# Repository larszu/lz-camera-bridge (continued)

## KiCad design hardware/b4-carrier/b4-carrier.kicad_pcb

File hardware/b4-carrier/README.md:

# B4 lens carrier board v1

A 184 × 100 mm two-layer carrier for the bench circuit in
[`docs/b4/iris-anleitung.html`](../../docs/b4/iris-anleitung.html): everything
that was loose on two breadboards on 2026-10-10, on one board with plug-in
modules and locking connectors.

**Status: generated, not built.** Fully routed (Freerouting, 0 open
connections); KiCad DRC has no errors apart from the deliberate triple ESP32 row
(see below), only silkscreen warnings. Nothing on this board has been powered.
Measure the first one before a lens is connected.

There is **no KiCad schematic** (`.kicad_sch`) yet: the netlist lives in
`generate_pcb.py`, one `place()` / `res()` call per part with its nets — that is
the reviewable source. The stage formulas are in the table below.

## What is on it

| Block | Parts | Why |
|---|---|---|
| Power in | USB-C with **CH224A** (24 kΩ on CFG1 = 12 V, WCH datasheet table 5-1), or a 5.5/2.1 mm DC jack; both through 1N5822 Schottky diodes | PD supply like the bench, DC as a fallback |
| Protection | Polyfuse MF-RHT200 (2 A hold), TVS P6KE18A, 470 µF bulk | Motor current spikes, short, over-voltage |
| 9 V | L7809 + 330 nF / 100 nF / 10 µF | Replaces the 330 Ω / 1 kΩ divider; the zoom stop hung on that voltage |
| 5 V | RECOM R-78E5.0-0.5 switcher → ESP32 VIN through 1N5819 | The ESP32's USB can stay plugged in |
| 3.3 V (quiet) | LP2950CZ-3.3 from 5 V | DAC, ADC, OLED, pots and the iris offset, separate from the ESP32's noisy 3.3 V |
| Op-amps | **LM324** in a socket | A: iris stage as on the bench. B: zoom. C: focus. D: unused, tied off |
| Zoom / focus drive | Difference amplifier `Vout = REF + 1.8 · (V_B − V_C)` with 100k/180k, REF = the demand socket's own 5 V centre (zoom socket pin 7); simulated in [`simulation/`](simulation/README.md) | "Stop" is now the lens's own reference when DAC B = DAC C, instead of a code that wandered 1270 … 1790 on the bench |
| Readback | 100 k / 68 k + 100 nF into ADS1115 A0–A3 (iris position, zoom position, focus position, iris setpoint) | As measured on the bench |
| Modules | **Either** ESP32 DevKit V1 (30 pin) **or** Waveshare ESP32-S3-ETH (with or without PoE module), Adafruit MCP4728, ADS1115 breakout, 0.96″ SSD1306 OLED — all on sockets | Swappable, and the DevKit's USB stays reachable |
| Pots | Three on-board 10 k (Alps RK09K: iris, zoom, focus), three JST-XH for external pots; jumpers JP2 / JP3 / JP4 choose on-board or external | Bench test without anything plugged in |
| Connectors | JST-XH, locking | Loose Dupont wires caused every fault on the bench |

## Connectors

| Ref | To | Pins (1 → n) |
|---|---|---|
| J3 | Lens Hirose 12-pin | +12 V (pin 6) · GND (3) · iris control (5) · iris position (7) · remote (8) · zoom position (10) · focus position (11) · pin 12 |
| J7 | Black zoom socket on the grip | GND · pin 6 (speed) · pin 7 (5 V centre, **REF**) · pin 9 (position) |
| J8 | Focus module socket | GND · control · REF · position — **pinout still to be measured** |
| J4 / J5 / J6 | External pots iris / zoom / focus | 3.3 V · wiper · GND |
| JP1 | Jumper: iris remote | On = pin 8 at 5 V through 1 kΩ |

## ESP32 DevKit V1: three widths

DOIT DevKit V1 clones exist with 22.86, 25.40 and 27.94 mm between the pin
rows. The 3V3 row (J10) is fixed; the VIN row is laid out three times (J11–J13).
**Solder a socket into only the one that fits your board.** DRC reports the
three as overlapping courtyards — that is intended. Measure: centre of one pin
row to the centre of the other.

## Waveshare ESP32-S3-ETH instead of the DevKit

J14 / J15: 2 × 20 pins, rows 17.78 mm apart, front side (RJ45) up, RJ45 end
towards the top edge (Waveshare's dimension drawing). The optional PoE module
plugs onto the 6-pin header on the top side, so it does not touch the carrier.
Connections: VSYS ← 5 V (through D4), IO16 SDA, IO17 SCL, IO1 / IO2 / IO3 the
iris / zoom / focus pots (camera-header pins — free while no camera is fitted).
The lens still needs the board's 12 V; PoE only powers the ESP32 board.
**Fit only one ESP32 board.**

## Firmware changes this board needs

* Zoom: DAC C fixed at mid-scale (2048); zoom speed = DAC B − DAC C. The stored
  stop becomes ≈ 2048 and should no longer wander; the position hold stays as
  a safety net.
* Focus: DAC D against DAC C, same scheme.
* OLED: SSD1306 on the existing I²C bus (0x3C) — WLAN, IP, iris ≈ F, zoom ≈ mm.
* Pots: DevKit GPIO 34 / 35 / 36, S3-ETH GPIO 1 / 2 / 3.

## Regenerate

```
/Applications/KiCad/KiCad.app/Contents/Frameworks/Python.framework/Versions/3.9/bin/python3 \
    hardware/b4-carrier/generate_pcb.py --route
```

Needs KiCad 10, Java (`brew install openjdk`) and Freerouting in `.tools/`
(not committed). The script writes the board, `bom.csv` and routes it.
`fab/` holds the files for PCBWay:

| File | What |
|---|---|
| `fab/b4-carrier-gerber.zip` | Gerbers + Excellon drill, upload as is |
| `fab/bom-smt.csv`, `fab/cpl-smt.csv` | SMT assembly of J1, U1, R1, C1 only |
| `bom.csv` | Every part with value and footprint, for ordering the through-hole parts |
| `fab/render-top.png`, `fab/render-bottom.png` | 3D renders |
| `fab/top-assembly.pdf` | Top copper, silkscreen and the module outlines (F.Fab) for placing parts |

Module outlines (ESP32, MCP4728, ADS1115) are drawn on F.Fab so nothing tall
ends up under a module on its header. The ADS1115 body is assumed to lie left of
its header (header on the module's right edge, VDD at the bottom) as on the
module used on the bench — check yours.

## Before ordering

1. Open `b4-carrier.kicad_pcb` in KiCad, look at every connector against the
   part you have (OLED pin order varies between modules!).
2. Check the ESP32 row width on your DevKit.
3. Order 2-layer, 1.6 mm, HASL, with **SMT assembly for J1, U1, R1, C1 only**
   (USB-C, CH224A and its two parts); everything else is through-hole.

## Ideas for v2 (not on this board)

* **Outputs off at power-up:** an analog switch (e.g. 74HC4066) in pin 5 and the
  zoom/focus lines, enabled by the firmware once the DAC holds sane values — no
  twitch while the ESP32 boots.
* **Lens current monitor** (INA219 on the I²C bus): a jammed servo or a short
  shows up as current, not as a burnt polyfuse.
* **VTR / RET buttons** to the lens via PC817 optocouplers (in stock).
* **ESD protection** (TVS array) on every line that leaves the board.
* A **touch panel** as a separate device using the HTTP API (see the B4 docs).

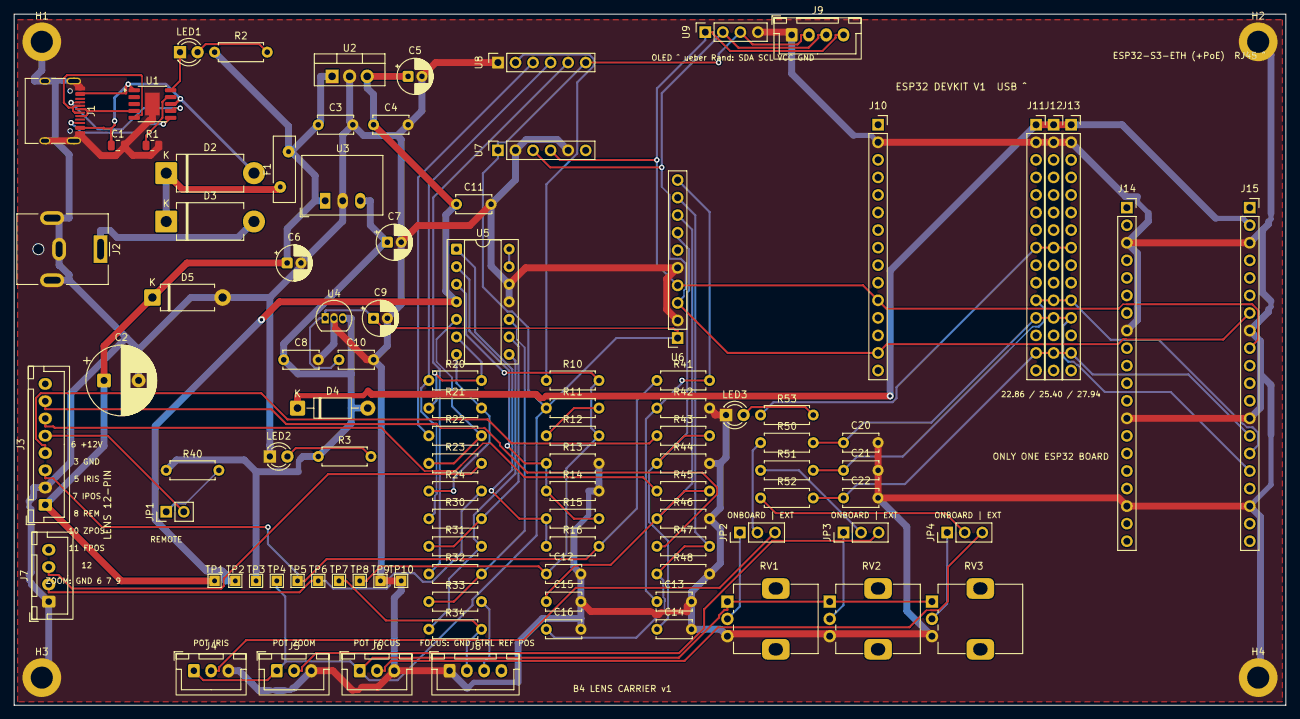
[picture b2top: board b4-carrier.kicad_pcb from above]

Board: 2 copper layers, 184.0 x 100.0 mm, 105 parts (0 on the bottom side), 62 nets.

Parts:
C1: 1uF 25V; C_0805_2012Metric
C2: 470uF 25V; CP_Radial_D10.0mm_P5.00mm
C3: 330nF; C_Disc_D5.0mm_W2.5mm_P5.00mm
C4, C10, C11, C12, C13, C14, C15, C16, C20, C21, C22: 100nF; C_Disc_D5.0mm_W2.5mm_P5.00mm
C5, C6: 10uF 25V; CP_Radial_D5.0mm_P2.00mm
C7: 22uF 16V; CP_Radial_D5.0mm_P2.00mm
C8: 1uF; C_Disc_D5.0mm_W2.5mm_P5.00mm
C9: 10uF 16V; CP_Radial_D5.0mm_P2.00mm
D2, D3: 1N5822; D_DO-201AD_P12.70mm_Horizontal
D4: 1N5819; D_DO-41_SOD81_P10.16mm_Horizontal
D5: P6KE18A; D_DO-15_P10.16mm_Horizontal
F1: MF-RHT200; Fuse_Bourns_MF-RHT200
H1, H2, H3, H4: M3; MountingHole_3.2mm_M3_DIN965_Pad
J1: USB-C PD 12V; USB_C_Receptacle_HRO_TYPE-C-31-M-12
J2: DC 12V; BarrelJack_CUI_PJ-063AH_Horizontal
J3: LENS 12-pin; JST_XH_B8B-XH-A_1x08_P2.50mm_Vertical
J4: POT IRIS; JST_XH_B3B-XH-A_1x03_P2.50mm_Vertical
J5: POT ZOOM; JST_XH_B3B-XH-A_1x03_P2.50mm_Vertical
J6: POT FOCUS; JST_XH_B3B-XH-A_1x03_P2.50mm_Vertical
J7: ZOOM DEMAND; JST_XH_B4B-XH-A_1x04_P2.50mm_Vertical
J8: FOCUS DEMAND; JST_XH_B4B-XH-A_1x04_P2.50mm_Vertical
J9: OLED cable; JST_XH_B4B-XH-A_1x04_P2.50mm_Vertical
J10: ESP32 L; PinSocket_1x15_P2.54mm_Vertical
J11: ESP32 R 22.86; PinSocket_1x15_P2.54mm_Vertical
J12: ESP32 R 25.40; PinSocket_1x15_P2.54mm_Vertical
J13: ESP32 R 27.94; PinSocket_1x15_P2.54mm_Vertical
J14: S3-ETH IO20 row; PinSocket_1x20_P2.54mm_Vertical
J15: S3-ETH VBUS row; PinSocket_1x20_P2.54mm_Vertical
JP1: REMOTE; PinHeader_1x02_P2.54mm_Vertical
JP2: IRIS POT; PinHeader_1x03_P2.54mm_Vertical
JP3: ZOOM POT; PinHeader_1x03_P2.54mm_Vertical
JP4: FOCUS POT; PinHeader_1x03_P2.54mm_Vertical
LED1: green; LED_D3.0mm
LED2: red; LED_D3.0mm
LED3: blue; LED_D3.0mm
R1: 24k 1%; R_0805_2012Metric
R2: 4.7k; R_Axial_DIN0207_L6.3mm_D2.5mm_P7.62mm_Horizontal
R3, R16, R40, R50, R51, R52: 1k; R_Axial_DIN0207_L6.3mm_D2.5mm_P7.62mm_Horizontal
R10, R11, R13, R15: 10k; R_Axial_DIN0207_L6.3mm_D2.5mm_P7.62mm_Horizontal
R12: 5.6k; R_Axial_DIN0207_L6.3mm_D2.5mm_P7.62mm_Horizontal
R14, R20, R22, R30, R32, R41, R43, R45, R47: 100k; R_Axial_DIN0207_L6.3mm_D2.5mm_P7.62mm_Horizontal
R21, R23, R31, R33: 180k; R_Axial_DIN0207_L6.3mm_D2.5mm_P7.62mm_Horizontal
R24, R34: 1.2k; R_Axial_DIN0207_L6.3mm_D2.5mm_P7.62mm_Horizontal
R42, R44, R46, R48: 68k; R_Axial_DIN0207_L6.3mm_D2.5mm_P7.62mm_Horizontal
R53: 330; R_Axial_DIN0207_L6.3mm_D2.5mm_P7.62mm_Horizontal
RV1: 10k lin IRIS; Potentiometer_Alps_RK09K_Single_Vertical
RV2: 10k lin ZOOM; Potentiometer_Alps_RK09K_Single_Vertical
RV3: 10k lin FOCUS; Potentiometer_Alps_RK09K_Single_Vertical
TP1: V12; TestPoint_THTPad_1.5x1.5mm_Drill0.7mm
TP2: V9; TestPoint_THTPad_1.5x1.5mm_Drill0.7mm
TP3: V5; TestPoint_THTPad_1.5x1.5mm_Drill0.7mm
TP4: A3V3; TestPoint_THTPad_1.5x1.5mm_Drill0.7mm
TP5: IRIS_CTRL; TestPoint_THTPad_1.5x1.5mm_Drill0.7mm
TP6: ZOOM_CTRL; TestPoint_THTPad_1.5x1.5mm_Drill0.7mm
TP7: FOCUS_CTRL; TestPoint_THTPad_1.5x1.5mm_Drill0.7mm
TP8: I_P; TestPoint_THTPad_1.5x1.5mm_Drill0.7mm
TP9, TP10: GND; TestPoint_THTPad_1.5x1.5mm_Drill0.7mm
U1: CH224A; SSOP-10-1EP_3.9x4.9mm_P1mm_EP2.1x3.3mm
U2: L7809; TO-220-3_Vertical
U3: R-78E5.0-0.5; Converter_DCDC_RECOM_R-78E-0.5_THT
U4: LP2950CZ-3.3; TO-92_Inline
U5: LM324; DIP-14_W7.62mm_Socket
U6: ADS1115; PinSocket_1x10_P2.54mm_Vertical
U7: MCP4728 JP1; PinSocket_1x06_P2.54mm_Vertical
U8: MCP4728 JP2; PinSocket_1x06_P2.54mm_Vertical
U9: OLED; PinSocket_1x04_P2.54mm_Vertical

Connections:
A3V3: C9.1, C10.1, J4.1, J5.1, J6.1, J9.2, R11.1, RV1.1, RV2.1, RV3.1, TP4.1, U4.1, U6.1, U7.1, U8.6, U9.3
ADC0: C14.1, R43.2, R44.1, U6.7
ADC1: C15.1, R45.2, R46.1, U6.8
ADC2: C16.1, R47.2, R48.1, U6.9
ADC3: C13.1, R41.2, R42.1, U6.10
CC1: J1.A5, U1.7
CC2: J1.B5, U1.6
CFG1: R1.1, U1.9
DAC_A: R10.1, U8.2
DAC_B: R22.1, U8.3
DAC_C: R20.1, R30.1, U8.4
DAC_D: R32.1, U8.5
DM: J1.A7, J1.B7, U1.5
DP: J1.A6, J1.B6, U1.4
D_OUT: U5.13, U5.14
ESP_VIN: D4.1, J11.1, J12.1, J13.1, J15.2
EXT_F: J6.2, JP4.3
EXT_I: J4.2, JP2.3
EXT_Z: J5.2, JP3.3
FOCUS_CTRL: J8.2, R34.2, TP7.1
FOCUS_POS: J3.7, R47.1
FREF: J8.3, R33.2
F_N: R30.2, R31.1, U5.9
F_OUT: R31.2, R34.1, U5.8
F_P: R32.2, R33.1, U5.10
GND: C1.2, C2.2, C3.2, C4.2, C5.2, C6.2, C7.2, C8.2, C9.2, C10.2, C11.2, C12.2, C13.2, C14.2, C15.2, C16.2, C20.2, C21.2, C22.2, D5.2, H1.1, H2.1, H3.1, H4.1, J1.A1, J1.A12, J1.B1, J1.B12, J1.SH, J2.2, J2.MP, J3.2, J4.3, J5.3, J6.3, J7.1, J8.1, J9.1, J10.2, J11.2, J12.2, J13.2, J14.3, J14.8, J14.13, J14.18, J15.3, J15.8, J15.13, J15.18, LED2.1, LED3.1, R1.2, R13.2, R14.2, R42.2, R44.2, R46.2, R48.2, RV1.3, RV2.3, RV3.3, TP9.1, TP10.1, U1.11, U2.2, U3.2, U4.2, U5.11, U5.12, U6.2, U6.5, U7.2, U7.5, U8.1, U9.4
IRIS_CTRL: J3.3, R16.2, R41.1, TP5.1
IRIS_POS: J3.4, R43.1
I_N: R13.1, R14.1, R15.2, U5.2
I_OUT: R15.1, R16.1, U5.1
I_P: C12.1, R10.2, R12.2, TP8.1, U5.3
I_RA: R11.2, R12.1
LED_STAT: J11.8, J12.8, J13.8, R53.1
PF: JP4.2, R52.1
PG: LED1.1, U1.10
PGLED: LED1.2, R2.2
PI: JP2.2, R50.1
POT_F: C22.1, J11.14, J12.14, J13.14, J15.14, R52.2
POT_I: C20.1, J11.12, J12.12, J13.12, J15.16, R50.2
POT_Z: C21.1, J11.11, J12.11, J13.11, J15.15, R51.2
PWRLED: LED2.2, R3.2
PZ: JP3.2, R51.1
REMOTE: J3.5, JP1.2
REM_J: JP1.1, R40.2
RV1W: JP2.1, RV1.2
RV2W: JP3.1, RV2.2
RV3W: JP4.1, RV3.2
SCL: J9.3, J10.14, J15.7, U6.3, U7.3, U9.2
SDA: J9.4, J10.11, J15.9, U6.4, U7.4, U9.1
STATLED: LED3.2, R53.2
V5: C7.1, C8.1, D4.2, R3.1, R40.1, TP3.1, U3.3, U4.3
V9: C4.1, C5.1, C11.1, TP2.1, U2.3, U5.4
V12: C2.1, C3.1, C6.1, D5.1, F1.2, J3.1, R2.1, TP1.1, U2.1, U3.1
VBUS: C1.1, D2.2, J1.A4, J1.A9, J1.B4, J1.B9, U1.1, U1.8
VDC: D3.2, J2.1
VIN12: D2.1, D3.1, F1.1
ZOOM_CTRL: J7.2, R24.2, TP6.1
ZOOM_POS: J3.6, R45.1
ZREF: J7.3, R23.2
Z_N: R20.2, R21.1, U5.6
Z_OUT: R21.2, R24.1, U5.7
Z_P: R22.2, R23.1, U5.5

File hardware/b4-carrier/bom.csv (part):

Ref,Value,Footprint,Note
"H1","M3","MountingHole:MountingHole_3.2mm_M3_DIN965_Pad",""
"H2","M3","MountingHole:MountingHole_3.2mm_M3_DIN965_Pad",""
"H3","M3","MountingHole:MountingHole_3.2mm_M3_DIN965_Pad",""
"H4","M3","MountingHole:MountingHole_3.2mm_M3_DIN965_Pad",""
"J1","USB-C PD 12V","Connector_USB:USB_C_Receptacle_HRO_TYPE-C-31-M-12","HRO TYPE-C-31-M-12 (LCSC C165948), SMT by PCBWay"
"U1","CH224A","Package_SO:SSOP-10-1EP_3.9x4.9mm_P1mm_EP2.1x3.3mm","WCH CH224A ESSOP-10, PD sink; SMT by PCBWay"
"R1","24k 1%","Resistor_SMD:R_0805_2012Metric","CFG1 -> 12 V (WCH datasheet table 5-1)"
"C1","1uF 25V","Capacitor_SMD:C_0805_2012Metric","VHV decoupling"
"LED1","green","LED_THT:LED_D3.0mm","PD power good"
"R2","4.7k","Resistor_THT:R_Axial_DIN0207_L6.3mm_D2.5mm_P7.62mm_Horizontal",""
"J2","DC 12V","Connector_BarrelJack:BarrelJack_CUI_PJ-063AH_Horizontal","5.5/2.1 mm, alternative to USB-C"
"D2","1N5822","Diode_THT:D_DO-201AD_P12.70mm_Horizontal","OR-ing, USB-C path"
"D3","1N5822","Diode_THT:D_DO-201AD_P12.70mm_Horizontal","OR-ing, DC jack path"
"F1","MF-RHT200","Fuse:Fuse_Bourns_MF-RHT200","2 A hold, lens + board"
"D5","P6KE18A","Diode_THT:D_DO-15_P10.16mm_Horizontal","TVS, cathode to +12 V"
"C2","470uF 25V","Capacitor_THT:CP_Radial_D10.0mm_P5.00mm","bulk for motor current"
"J3","LENS 12-pin","Connector_JST:JST_XH_B8B-XH-A_1x08_P2.50mm_Vertical","to Hirose HR10 12-pin: 6, 3, 5, 7, 8, 10, 11, 12"
"U2","L7809","Package_TO_SOT_THT:TO-220-3_Vertical","9 V for the LM324"
"C3","330nF","Capacitor_THT:C_Disc_D5.0mm_W2.5mm_P5.00mm",""
"C4","100nF","Capacitor_THT:C_Disc_D5.0mm_W2.5mm_P5.00mm",""
"C5","10uF 25V","Capacitor_THT:CP_Radial_D5.0mm_P2.00mm",""
"U3","R-78E5.0-0.5","Converter_DCDC:Converter_DCDC_RECOM_R-78E-0.5_THT","5 V switcher for the ESP32"
"C6","10uF 25V","Capacitor_THT:CP_Radial_D5.0mm_P2.00mm",""
"C7","22uF 16V","Capacitor_THT:CP_Radial_D5.0mm_P2.00mm",""
"U4","LP2950CZ-3.3","Package_TO_SOT_THT:TO-92_Inline","quiet 3.3 V: DAC, ADC, OLED, pots"
"C8","1uF","Capacitor_THT:C_Disc_D5.0mm_W2.5mm_P5.00mm",""
"C9","10uF 16V","Capacitor_THT:CP_Radial_D5.0mm_P2.00mm",""
"C10","100nF","Capacitor_THT:C_Disc_D5.0mm_W2.5mm_P5.00mm",""
"D4","1N5819","Diode_THT:D_DO-41_SOD81_P10.16mm_Horizontal","no back-feed from the ESP32's USB"
"LED2","red","LED_THT:LED_D3.0mm","5 V present"
"R3","1k","Resistor_THT:R_Axial_DIN0207_L6.3mm_D2.5mm_P7.62mm_Horizontal",""
"U5","LM324","Package_DIP:DIP-14_W7.62mm_Socket","in a socket"
"C11","100nF","Capacitor_THT:C_Disc_D5.0mm_W2.5mm_P5.00mm",""
"R10","10k","Resistor_THT:R_Axial_DIN0207_L6.3mm_D2.5mm_P7.62mm_Horizontal",""
"R11","10k","Resistor_THT:R_Axial_DIN0207_L6.3mm_D2.5mm_P7.62mm_Horizontal","Ra1; 22k for full range"
"R12","5.6k","Resistor_THT:R_Axial_DIN0207_L6.3mm_D2.5mm_P7.62mm_Horizontal","Ra2; 6.8k for full range"
"R13","10k","Resistor_THT:R_Axial_DIN0207_L6.3mm_D2.5mm_P7.62mm_Horizontal",""
"R14","100k","Resistor_THT:R_Axial_DIN0207_L6.3mm_D2.5mm_P7.62mm_Horizontal","DNP parallel to R13, full range only"
"R15","10k","Resistor_THT:R_Axial_DIN0207_L6.3mm_D2.5mm_P7.62mm_Horizontal",""
"R16","1k","Resistor_THT:R_Axial_DIN0207_L6.3mm_D2.5mm_P7.62mm_Horizontal",""
"C12","100nF","Capacitor_THT:C_Disc_D5.0mm_W2.5mm_P5.00mm",""
"R20","100k","Resistor_THT:R_Axial_DIN0207_L6.3mm_D2.5mm_P7.62mm_Horizontal",""
"R21","180k","Resistor_THT:R_Axial_DIN0207_L6.3mm_D2.5mm_P7.62mm_Horizontal",""
"R22","100k","Resistor_THT:R_Axial_DIN0207_L6.3mm_D2.5mm_P7.62mm_Horizontal",""
"R23","180k","Resistor_THT:R_Axial_DIN0207_L6.3mm_D2.5mm_P7.62mm_Horizontal",""
"R24","1.2k","Resistor_THT:R_Axial_DIN0207_L6.3mm_D2.5mm_P7.62mm_Horizontal",""
"R30","100k","Resistor_THT:R_Axial_DIN0207_L6.3mm_D2.5mm_P7.62mm_Horizontal",""
"R31","180k","Resistor_THT:R_Axial_DIN0207_L6.3mm_D2.5mm_P7.62mm_Horizontal",""
"R32","100k","Resistor_THT:R_Axial_DIN0207_L6.3mm_D2.5mm_P7.62mm_Horizontal",""
"R33","180k","Resistor_THT:R_Axial_DIN0207_L6.3mm_D2.5mm_P7.62mm_Horizontal",""
"R34","1.2k","Resistor_THT:R_Axial_DIN0207_L6.3mm_D2.5mm_P7.62mm_Horizontal",""
"R41","100k","Resistor_THT:R_Axial_DIN0207_L6.3mm_D2.5mm_P7.62mm_Horizontal",""
"R42","68k","Resistor_THT:R_Axial_DIN0207_L6.3mm_D2.5mm_P7.62mm_Horizontal",""
"R43","100k","Resistor_THT:R_Axial_DIN0207_L6.3mm_D2.5mm_P7.62mm_Horizontal",""
"R44","68k","Resistor_THT:R_Axial_DIN0207_L6.3mm_D2.5mm_P7.62mm_Horizontal",""
"R45","100k","Resistor_THT:R_Axial_DIN0207_L6.3mm_D2.5mm_P7.62mm_Horizontal",""
"R46","68k","Resistor_THT:R_Axial_DIN0207_L6.3mm_D2.5mm_P7.62mm_Horizontal",""
"R47","100k","Resistor_THT:R_Axial_DIN0207_L6.3mm_D2.5mm_P7.62mm_Horizontal",""
"R48","68k","Resistor_THT:R_Axial_DIN0207_L6.3mm_D2.5mm_P7.62mm_Horizontal",""
"C13","100nF","Capacitor_THT:C_Disc_D5.0mm_W2.5mm_P5.00mm",""
"C14","100nF","Capacitor_THT:C_Disc_D5.0mm_W2.5mm_P5.00mm",""
"C15","100nF","Capacitor_THT:C_Disc_D5.0mm_W2.5mm_P5.00mm",""
"C16","100nF","Capacitor_THT:C_Disc_D5.0mm_W2.5mm_P5.00mm",""
"R40","1k","Resistor_THT:R_Axial_DIN0207_L6.3mm_D2.5mm_P7.62mm_Horizontal",""
"JP1","REMOTE","Connector_PinHeader_2.54mm:PinHeader_1x02_P2.54mm_Vertical","jumper on = iris remote (pin 8)"
"U8","MCP4728 JP2","Connector_PinSocket_2.54mm:PinSocket_1x06_P2.54mm_Vertical","Adafruit 4470, row JP2: GND VA VB VC VD VCC"
"U7","MCP4728 JP1","Connector_PinSocket_2.54mm:PinSocket_1x06_P2.54mm_Vertical","Adafruit 4470, row JP1: VCC GND SCL SDA LDAC RDY"
"U6","ADS1115","Connector_PinSocket_2.54mm:PinSocket_1x10_P2.54mm_Vertical","ADS1115 breakout: VDD GND SCL SDA ADDR ALRT A0 A1 A2 A3, VDD at the bottom"
"U9","OLED","Connector_PinSocket_2.54mm:PinSocket_1x04_P2.54mm_Vertical","0.96in SSD1306: module hangs over the board edge; check your module's pin order"
"J9","OLED cable","Connector_JST:JST_XH_B4B-XH-A_1x04_P2.50mm_Vertical","alternative: OLED on a cable in the case lid (GND VCC SCL SDA)"
"J10","ESP32 L","Connector_PinSocket_2.54mm:PinSocket_1x15_P2.54mm_Vertical","ESP32 DevKit V1 3V3 row"
"J11","ESP32 R 22.86","Connector_PinSocket_2.54mm:PinSocket_1x15_P2.54mm_Vertical","VIN row at 22.86 mm - fit only the one your board needs"
"J12","ESP32 R 25.40","Connector_PinSocket_2.54mm:PinSocket_1x15_P2.54mm_Vertical","VIN row at 25.40 mm - fit only the one your board needs"
"J13","ESP32 R 27.94","Connector_PinSocket_2.54mm:PinSocket_1x15_P2.54mm_Vertical","VIN row at 27.94 mm - fit only the one your board needs"
"J14","S3-ETH IO20 row","Connector_PinSocket_2.54mm:PinSocket_1x20_P2.54mm_Vertical","ESP32-S3-ETH left row (IO20 ... IO33)"
"J15","S3-ETH VBUS row","Connector_PinSocket_2.54mm:PinSocket_1x20_P2.54mm_Vertical","ESP32-S3-ETH right row: VSYS <- 5 V, IO16 SDA, IO17 SCL, IO1/2/3 pots"
"LED3","blue","LED_THT:LED_D3.0mm","status, GPIO25"
"R53","330","Resistor_THT:R_Axial_DIN0207_L6.3mm_D2.5mm_P7.62mm_Horizontal",""
"RV1","10k lin IRIS","Potentiometer_THT:Potentiometer_Alps_RK09K_Single_Vertical","Alps RK09K"
"RV2","10k lin ZOOM","Potentiometer_THT:Potentiometer_Alps_RK09K_Single_Vertical","Alps RK09K with centre detent"
"JP2","IRIS POT","Connector_PinHeader_2.54mm:PinHeader_1x03_P2.54mm_Vertical","1-2 on-board, 2-3 external"
"JP3","ZOOM POT","Connector_PinHeader_2.54mm:PinHeader_1x03_P2.54mm_Vertical","1-2 on-board, 2-3 external"
"RV3","10k lin FOCUS","Potentiometer_THT:Potentiometer_Alps_RK09K_Single_Vertical","Alps RK09K"
"JP4","FOCUS POT","Connector_PinHeader_2.54mm:PinHeader_1x03_P2.54mm_Vertical","1-2 on-board, 2-3 external"
"R50","1k","Resistor_THT:R_Axial_DIN0207_L6.3mm_D2.5mm_P7.62mm_Horizontal",""
"R51","1k","Resistor_THT:R_Axial_DIN0207_L6.3mm_D2.5mm_P7.62mm_Horizontal",""
"R52","1k","Resistor_THT:R_Axial_DIN0207_L6.3mm_D2.5mm_P7.62mm_Horizontal",""
"C20","100nF","Capacitor_THT:C_Disc_D5.0mm_W2.5mm_P5.00mm",""
"C21","100nF","Capacitor_THT:C_Disc_D5.0mm_W2.5mm_P5.00mm",""
"C22","100nF","Capacitor_THT:C_Disc_D5.0mm_W2.5mm_P5.00mm",""
"J4","POT IRIS","Connector_JST:JST_XH_B3B-XH-A_1x03_P2.50mm_Vertical","3V3 / wiper / GND"
"J5","POT ZOOM","Connector_JST:JST_XH_B3B-XH-A_1x03_P2.50mm_Vertical","3V3 / wiper / GND"
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
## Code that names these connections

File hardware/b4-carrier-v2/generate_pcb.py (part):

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R("R3", "100", "VBAT", "BATP", 16.0, 24.0)
C("C20", "1nF 50V", "SDRV", "GND", 11.5, 25.0)
CORE = {"U2", "L1", "C2", "C3", "C4", "C5", "C6", "C7", "C8", "C9", "C10", "C11", "C12", "C13", "C14", "C15",
        "C16", "C17", "R2", "LED1", "R7"}   # R2 sits right in front of PROG (pin 20); C18, R3, C20 go to the legaliser
OFF[:] = [-4, -14]
R("R4", "5.23k", "REGN", "TS", 13, 40)
R("R5", "30.1k", "TS", "GND", 13, 43)
place("RT1", "NTC", "10k NTC 103AT", 41, 52, 0, {"1": "TS", "2": "GND"}, mpn="Semitec 103AT-2 or 10k B3435 0603, at the cells")
R("R6", "10k", "CHG_INT", "A3V3", 13, 46)
OFF[:] = [0, 0]
R("R7", "1k", "A3V3", "LED_CHG", 31.6, 27.25, rot=180)   # charge LED right next to STAT (pin 1)
place("LED1", "LED", "CHG", 28.3, 27.25, 0, {"1": "CHG_STAT", "2": "LED_CHG"}, mpn="0603 orange")
OFF[:] = [-4, -14]
place("TP1", "TP", "QON", 9, 41, pads={"1": "QON"})
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R("R19", "1.4k", "EF_ILM", "GND", 69, 9, mpn="1.40k 1%: ~1.5 A limit (datasheet ILIMIT table)")
R("R20", "100k", "V12", "EF_EN", 63, 16)
R("R21", "13.7k", "EF_EN", "GND", 66, 16, mpn="UVLO ~10 V")
place("Q1", "SOT23", "AO3400A", 70, 16, 0, {"1": "LENS_OFF", "2": "GND", "3": "EF_EN"}, mpn="AO3400A: GPIO high = lens power off")
R("R22", "100k", "LENS_OFF", "GND", 73, 16)
R("R23", "10k", "EF_FLT", "A3V3", 73, 12)
place("RS1", "R2512", "20mR", 77, 8, 0, {"1": "V12E", "2": "V12_LENS"}, mpn="20 mOhm 1% 2512, 1 W")
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R("R47", "100k", "DAC_D", "F_P", 61, 57)
R("R48", "180k", "F_P", "FREF", 64, 57)
R("R49", "1.2k", "F_OUT", "F_SW", 67, 57)
R("R50", "1k", "V5", "REM_SRC", 70, 51, mpn="pin 8 remote: 5 V through 1k (through the CD4066)")
# readback 100k/68k + 100nF
for i, (src, dst) in enumerate([("IRIS_CTRL", "ADC3"), ("IRIS_POS", "ADC0"), ("ZOOM_POS", "ADC1"), ("FOCUS_POS", "ADC2")]):
    R(f"R{51 + 2 * i}", "100k", src, dst, 73 + 3 * i, 51)
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dk_l = ["-", "GND", "-", "-", "BTN_LED", "-", "-", "-", "-", "STAT_LED", "SDA", "-", "-", "SCL", "-"]
dk_r = ["ESP_5V", "GND", "BTN_RET", "-", "TALLY_G", "TALLY_R", "LENS_OFF", "OUT_EN", "BTN_VTR", "TALLY_IN",
        "POT_Z", "POT_I", "CHG_INT", "POT_F", "-"]
# DevKit GPIOs: 4 BTN_LED, 16 EF_FLT, 19 STAT, 21 SDA, 22 SCL | VIN, 13 RET, 14 TALLY_G, 27 TALLY_R,
# 26 LENS_OFF, 25 OUT_EN, 33 VTR, 32 TALLY_IN, 35 POT_Z, 34 POT_I, 39 (VN) CHG_INT, 36 (VP) POT_F.
dk_l[5] = "EF_FLT"  # left row pin 6 = RX2 = GPIO16
place("J10", "S15", "DEVKIT 3V3 ROW", X0, Y0, 0, {str(i + 1): n for i, n in enumerate(dk_l) if n != "-"},
      smt=False, mpn="female header 1x15, DevKit V1")
for k, gap in enumerate([22.86, 25.40, 27.94]):
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    text(lbl, 33 + 2.5 * i, 83.4, 0.8, bold=False, rot=90)

# tally: two 12 V low-side outputs, one optocoupled input
place("U14", "SMDIP4", "PC817", 97, 59, 90, {"1": "TIN_A", "2": "TIN_N", "3": "GND", "4": "TALLY_IN"}, mpn="PC817C SMD")
R("R73", "2.2k", "TIN_P", "TIN_A", 93.5, 55, kind="R08", mpn="2.2k 0805: 5-24 V tally input")
R("R74", "10k", "TALLY_IN", "A3V3", 100.5, 55)
place("F2", "FUSE1206", "0.5A PTC", 97, 66, 0, {"1": "V12", "2": "TALLY_V"}, mpn="0.5 A hold PTC 1206")
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    text(lbl, 93 + 2.5 * i, 83.4, 0.8, bold=False, rot=90)

# pots: on-board or external per axis
for i, (ax, gpio) in enumerate([("I", "POT_I"), ("Z", "POT_Z"), ("F", "POT_F")]):
    x = 49.5 + i * 14.6
    name = ("IRIS", "ZOOM", "FOCUS")[i]
    place(f"RV{i + 1}", "POT", f"10k {name}", x, 74, 0, {"1": "A3V3", "2": f"RV{ax}W", "3": "GND"},
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

def charger_core():
    """U2 turned 180 deg at (20, 26): south pins PMID 29, SW1 28, GND 27, SW2 26, SYS 25 (0.45 mm)."""
    pm, s1, g27, s2, sy = (padxy("U2", n) for n in ("29", "28", "27", "26", "25"))
    yb = 28.9                                   # PMID / SYS buses run here, 0.7 mm below the pins
    # SW1 / SW2 leave the pin row at 0.25 mm and widen at once; the PGND via sits between them
    trk("SW1", [s1, (s1[0], 29.6), (s1[0] + 0.5, 30.1)], 0.25)   # narrow until clear of buses and PGND
    trk("SW1", [(s1[0] + 0.5, 30.1), (21.5, 30.65), padxy("L1", "1")], 0.8)
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    trk("VSYS", [(sy[0] - 0.3, yb), (padxy("C16", "1")[0], yb)], 0.6)
    for c in ("C17", "C12", "C13", "C14", "C15", "C16"):
        trk("VSYS", [(padxy(c, "1")[0], yb), padxy(c, "1")], 0.6)
    # VBAT pins 22/23 (west) bridged, out to C18; CHG_IN pins 2/3 and 8/9 (east) bridged
    v22, v23 = padxy("U2", "22"), padxy("U2", "23")
    trk("VBAT", [v22, v23], 0.2)
    ym = (v22[1] + v23[1]) / 2
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    trk("CHG_IN", [c8, c9], 0.2)
    ym = (c2[1] + c3[1]) / 2
    trk("CHG_IN", [(c2[0], ym), padxy("C7", "1")], 0.25)
    via("CHG_IN", 22.75, ym)                     # pins 2/3 reach the rest of CHG_IN through the planes
    trk("PROG", [padxy("U2", "20"), padxy("R2", "1")], 0.2)
    # D+/D- tied together at the pins
    trk("CHG_DPDM", [padxy("U2", "6"), padxy("U2", "7")], 0.2)
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
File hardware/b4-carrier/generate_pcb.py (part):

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cap("C15", "100nF", "ADC1", "GND", 77, 85)
cap("C16", "100nF", "ADC2", "GND", 77, 89)

# pin 8: remote via jumper
res("R40", "1k", "V5", "REM_J", 22, 66)
place("JP1", "H2", "REMOTE", 22, 72, 90, {"1": "REM_J", "2": "REMOTE"}, note="jumper on = iris remote (pin 8)")
text("REMOTE", 22, 76, 0.8)

# --- modules -----------------------------------------------------------------------
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text("ESP32-S3-ETH (+PoE)  RJ45 ^", S3X + 9, 6.0, 0.9)
text("ONLY ONE ESP32 BOARD", 150, 64, 0.9)

place("LED3", "LED", "blue", 103, 58, 0, {"1": "GND", "2": "STATLED"}, note="status, GPIO25")
res("R53", "330", "LED_STAT", "STATLED", 108, 58)

# --- pots: on-board (iris, zoom) or external, by jumper ---------------------------
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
